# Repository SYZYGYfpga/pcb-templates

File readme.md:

# SYZYGY PCB Templates

This repository contains schematics, PCB files and part libraries to use as a template for creating SYZYGY compliant peripherals. 

[More Information About SYZYGY](https://syzygyfpga.io/)

## Template Contains

* SYZYGY Standard and Transceiver Connectors
* MCU for SYZYGY DNA Support
* Programming Connector (Tag-Connect)
* Standard Mechanical Configuration (Board length can be adjusted as necessary)

## Tag-Connect Programming Header

The programming connection for the SYZYGY DNA MCU uses a connector-less [Tag-Connect header](https://www.tag-connect.com/). A wired connector with spring loaded contacts clips onto the board and connects to the headers exposed pads. The template's header design allows a programming connection from either side of the board.

The template boards support either the TC2030 or TC2030-NL. The exact cable model will depend on the programmer you are using as this changes the pinout and connector on the other end of the cable.

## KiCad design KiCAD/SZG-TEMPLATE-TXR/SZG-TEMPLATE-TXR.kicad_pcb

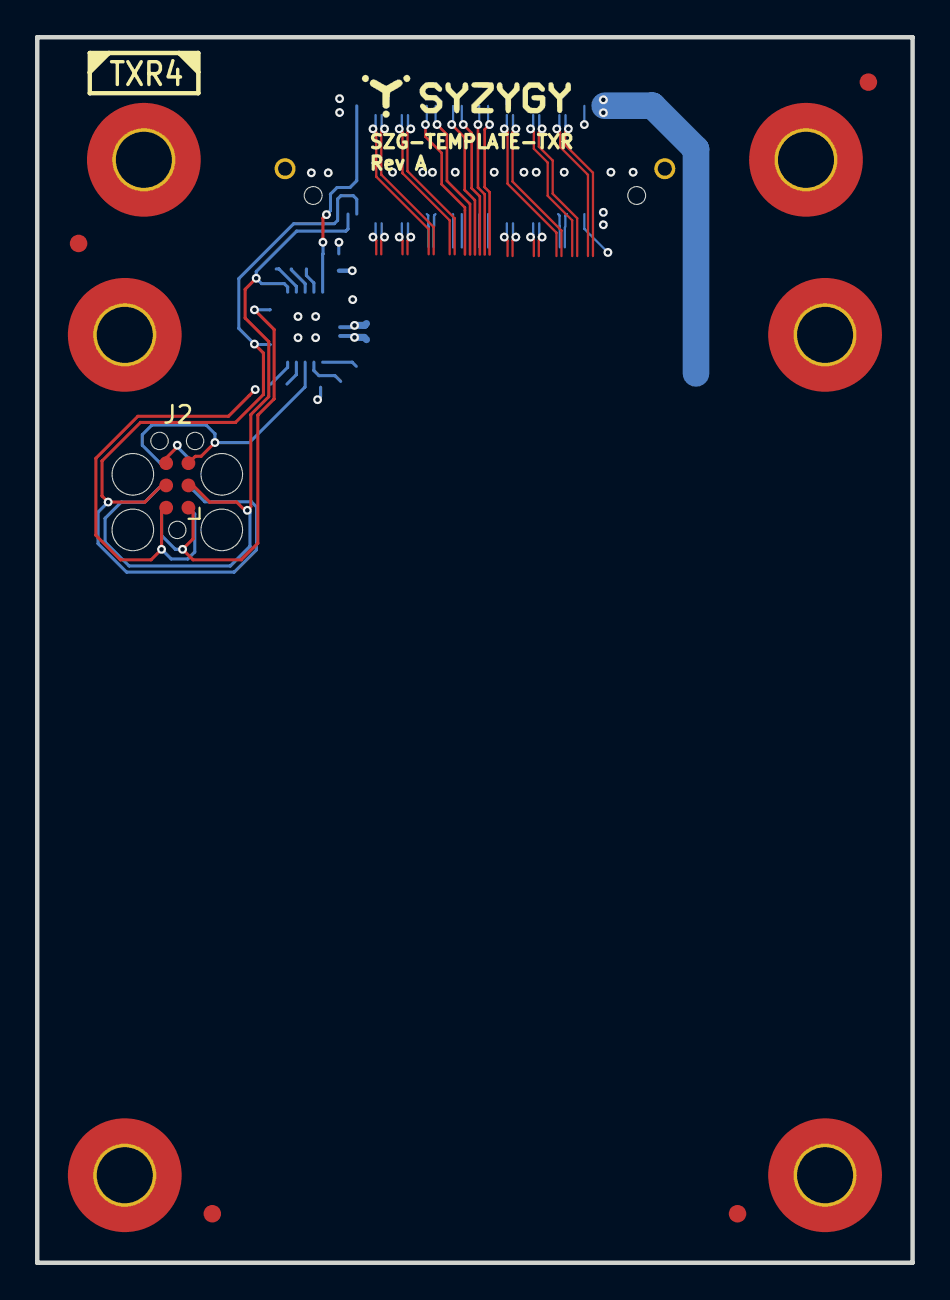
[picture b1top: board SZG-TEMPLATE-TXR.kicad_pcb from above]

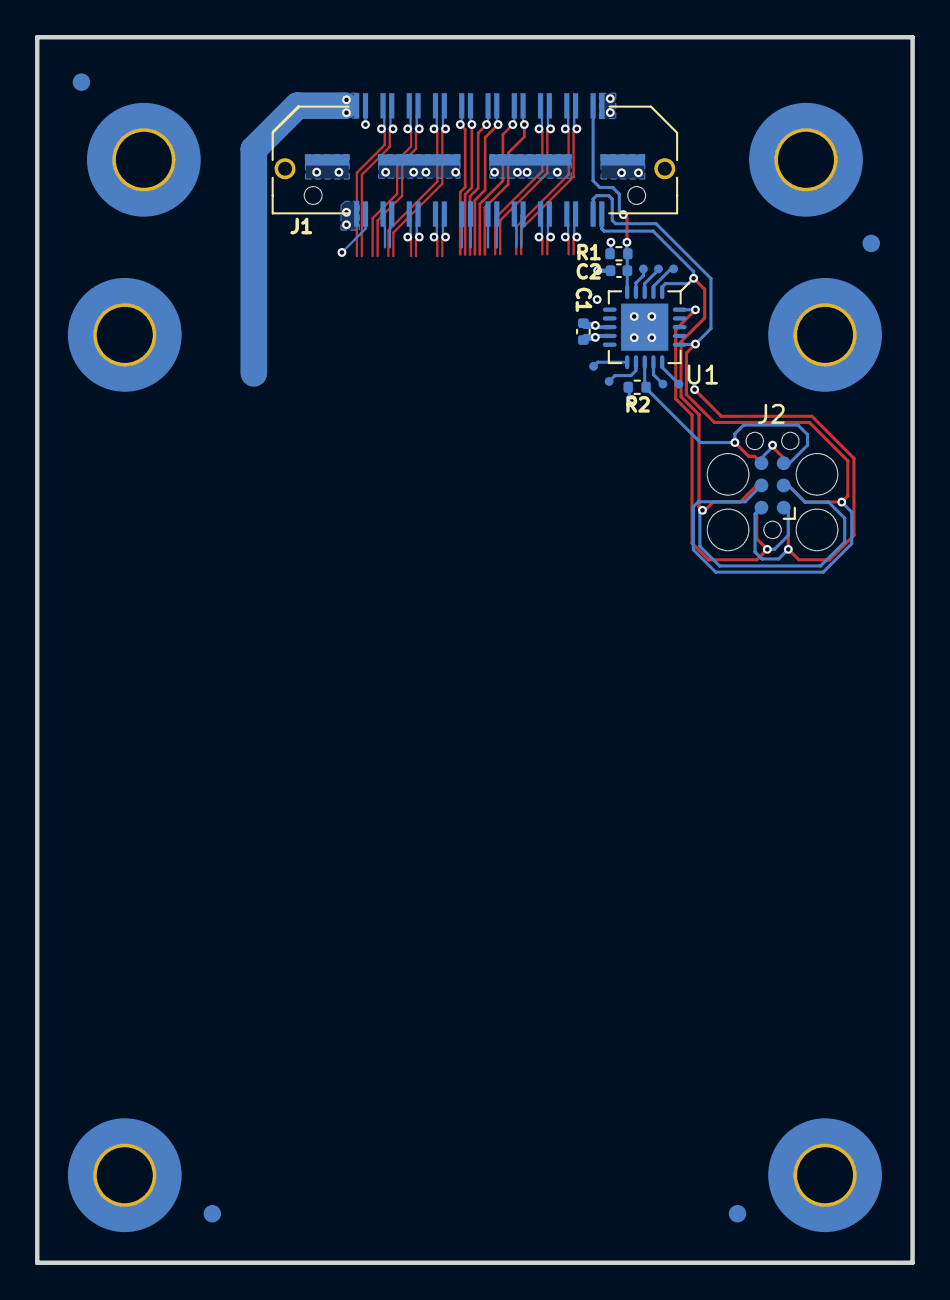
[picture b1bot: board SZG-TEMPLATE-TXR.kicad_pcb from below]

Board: 4 copper layers, 50.0 x 70.0 mm, 29 parts (17 on the bottom side), 14 nets.

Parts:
*1: Opal Kelly Logo; okLogo-23x5
C1: 0.1uF; C_0402_1005Metric
C2: 0.1uF DNP; C_0402_1005Metric
FID1, FID2, FID3, FID4, FID5, FID6, FID7, FID8: Fiducial; Fiducial_1mm_Mask2mm
H1, H2, H3, H4, H5, H6: MountingHole_Pad; MountingHole_3.2mm_M3_6.5mm_Pad_TopBottom
J1: SYZYGY_TXR-4; QTH-020-01-F-D-DP-A
J2: Conn_01x06; Tag-Connect_TC2030-IDC-FP_2x03_P1.27mm_Vertical
R1, R2: 10K; R_0402_1005Metric
TP5, TP6, TP7, TP8, TP9, TP10, TP11: TestPoint; TestPoint-20mil
U1: ATtiny44A-MU; QFN-24-4x4mm

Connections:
+3V3: C1.1, J1.40 (+3.3V), J2.2, R1.1, R2.1, U1.9 (VCC)
/MCU_MISO: J2.1, U1.20 (PA5)
/MCU_RESET_B: J2.5, R2.2, U1.13 (~RESET/PB3)
/MCU_SCL_USCK: J1.1 (SCL), J2.3, U1.1 (PA4)
/MCU_SDA_MOSI: J1.3 (SDA), J2.4, U1.16 (PA6)
/R_GA: C2.1, J1.4 (R_GA), R1.2, U1.5 (AREF/PA0)
GND: C1.2, C2.2, J1.0 (GND), J2.6, U1.8 (GND), U1.21 (GND)
unnamed: TP5.1, U1.11 (XTAL1/PB0)
unnamed: TP6.1, U1.4 (PA1)
unnamed: TP7.1, U1.12 (XTAL2/PB1)
unnamed: TP8.1, U1.3 (PA2)
unnamed: TP9.1, U1.14 (PB2)
unnamed: TP10.1, U1.2 (PA3)
unnamed: TP11.1, U1.15 (PA7)

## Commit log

2021-04-06 Initial commit. Adding KiCAD template projects for SYZYGY Standard and Transceiver pods.
2021-04-12 Corrected a net name. Improved example SYZYGY connector breakout routing for TXR board.
2021-04-12 Added main readme
2021-04-12 corrected image link
2021-04-13 Adjusted the readme board image size.
2021-04-13 Move link to Tag-Connect.
2021-04-13 Minor copy changes / fixes.
2021-04-13 Adding Altium template project files.
2021-04-14 Updated the template projects MCU programming header to use the standard Tag-Connect cable pin order.
2021-05-24 Updated Tag-Connect header footprint to remove paste mask openings.
2021-05-24 Improved SYZYGY TXR4 example breakout routing.
2022-08-04 Updated SZG-TEMPLATE-STD to KiCAD v6. Added STD port silk logo.
2022-08-04 Added -backups to gitignore.
2022-08-04 Fixed SZG-TEMPLATE-TXR board and mounting hole dimensions. Added TXR4 logo. Updated board images.
2022-08-04 Added the STD and TXR4 silk logo to Altium template PCBs.
